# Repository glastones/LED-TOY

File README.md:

# LED-TOY
All led are blinking slow RGB. At the start all are uniform but after some time start to deviate. 
Nice to watch it.

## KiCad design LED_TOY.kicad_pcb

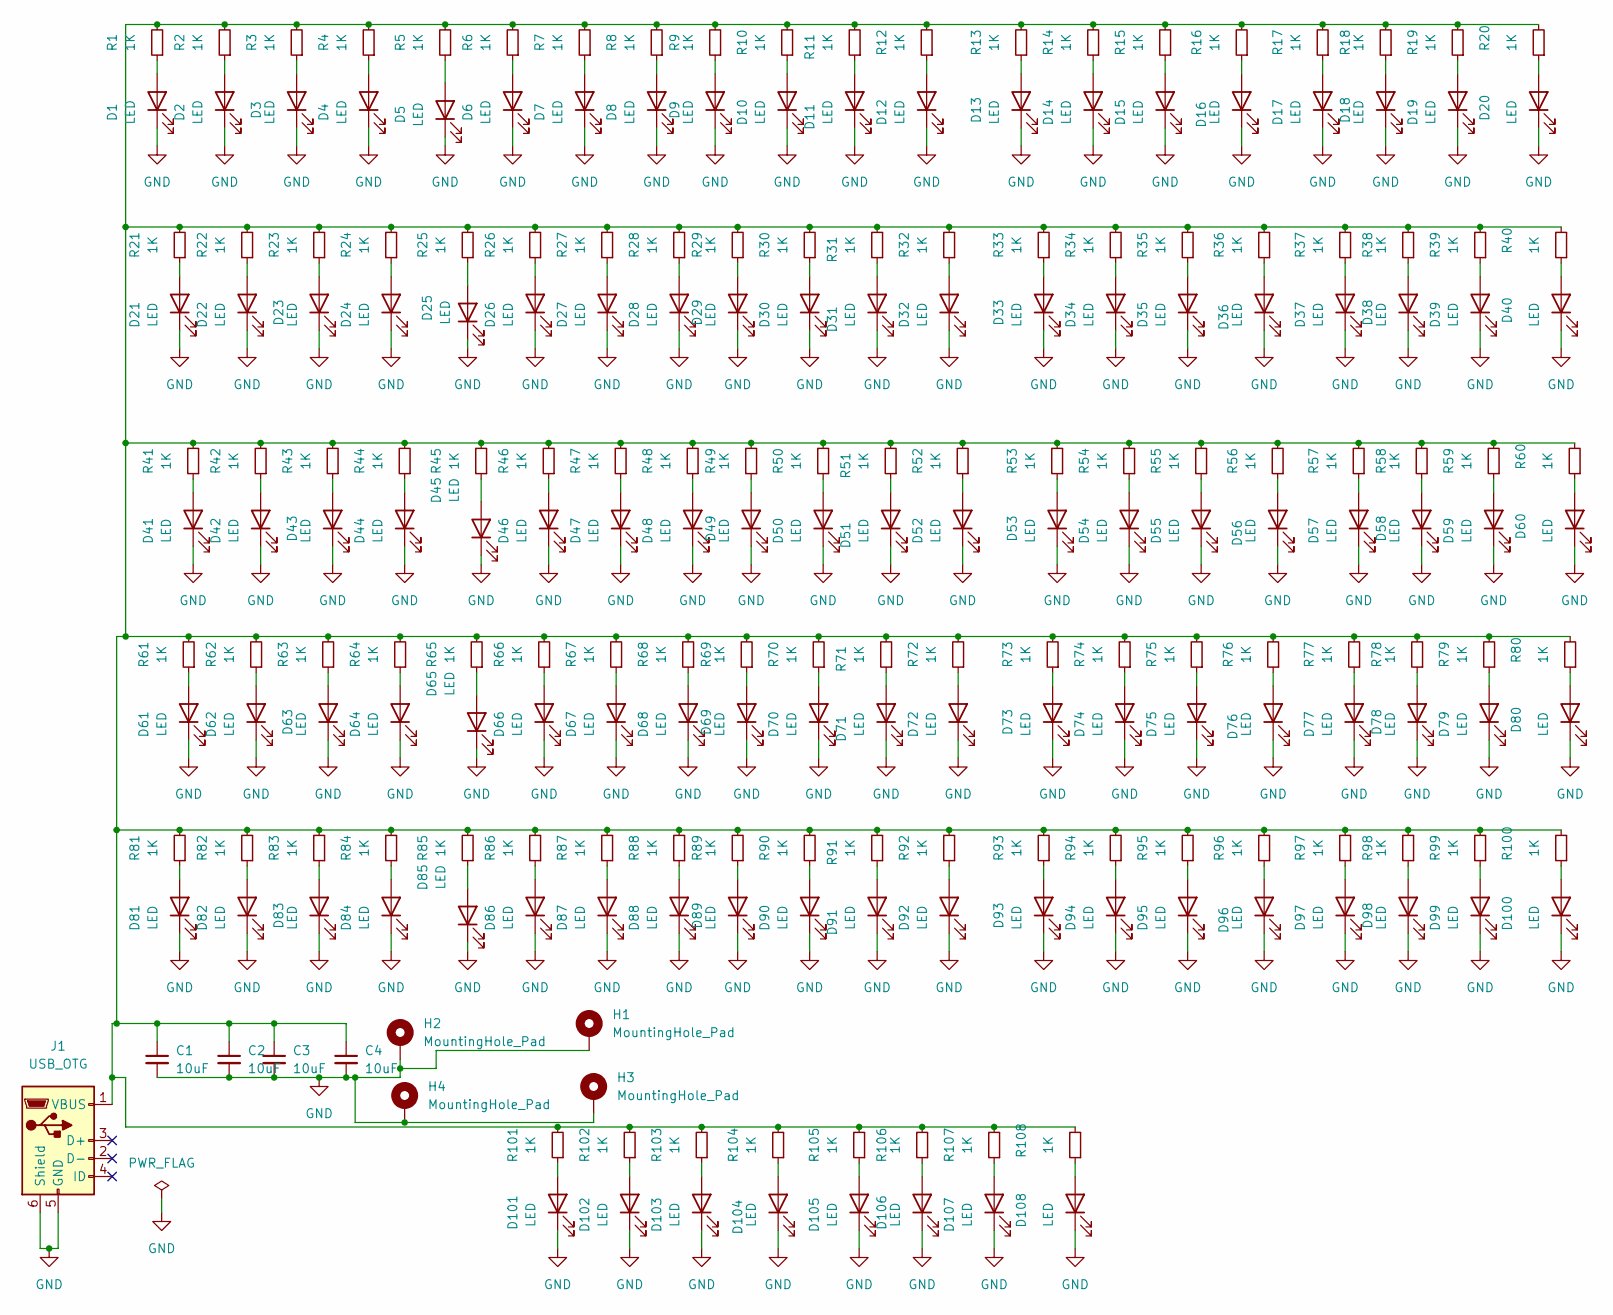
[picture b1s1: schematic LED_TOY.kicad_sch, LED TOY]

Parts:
C1, C2, C3, C4: 10uF; C_0805_2012Metric_Pad1.18x1.45mm_HandSolder
D1, D2, D3, D4, D5, D6, D7, D8, D9, D10, D11, D12, D13, D14, D15, D16, D17, D18, D19, D20, D21, D22, D23, D24, D25, D26, D27, D28, D29, D30, D31, D32, D33, D34, D35, D36, D37, D38, D39, D40, D41, D42, D43, D44, D45, D46, D47, D48, D49, D50, D51, D52, D53, D54, D55, D56, D57, D58, D59, D60, D61, D62, D63, D64, D65, D66, D67, D68, D69, D70, D71, D72, D73, D74, D75, D76, D77, D78, D79, D80, D81, D82, D83, D84, D85, D86, D87, D88, D89, D90, D91, D92, D93, D94, D95, D96, D97, D98, D99, D100, D101, D102, D103, D104, D105, D106, D107, D108: LED; LED_D5.0mm
H1, H2, H3, H4: MountingHole_Pad; MountingHole_2.7mm_Pad
J1: USB_OTG; USB_Mini-B_Lumberg_2486_01_Horizontal
R1, R2, R3, R4, R5, R6, R7, R8, R9, R10, R11, R12, R13, R14, R15, R16, R17, R18, R19, R20, R21, R22, R23, R24, R25, R26, R27, R28, R29, R30, R31, R32, R33, R34, R35, R36, R37, R38, R39, R40, R41, R42, R43, R44, R45, R46, R47, R48, R49, R50, R51, R52, R53, R54, R55, R56, R57, R58, R59, R60, R61, R62, R63, R64, R65, R66, R67, R68, R69, R70, R71, R72, R73, R74, R75, R76, R77, R78, R79, R80, R81, R82, R83, R84, R85, R86, R87, R88, R89, R90, R91, R92, R93, R94, R95, R96, R97, R98, R99, R100, R101, R102, R103, R104, R105, R106, R107, R108: 1K; R_0805_2012Metric_Pad1.20x1.40mm_HandSolder

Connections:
GND: C1.2, C2.2, C3.2, C4.2, D1.1 (K), D2.1 (K), D3.1 (K), D4.1 (K), D5.1 (K), D6.1 (K), D7.1 (K), D8.1 (K), D9.1 (K), D10.1 (K), D11.1 (K), D12.1 (K), D13.1 (K), D14.1 (K), D15.1 (K), D16.1 (K), D17.1 (K), D18.1 (K), D19.1 (K), D20.1 (K), D21.1 (K), D22.1 (K), D23.1 (K), D24.1 (K), D25.1 (K), D26.1 (K), D27.1 (K), D28.1 (K), D29.1 (K), D30.1 (K), D31.1 (K), D32.1 (K), D33.1 (K), D34.1 (K), D35.1 (K), D36.1 (K), D37.1 (K), D38.1 (K), D39.1 (K), D40.1 (K), D41.1 (K), D42.1 (K), D43.1 (K), D44.1 (K), D45.1 (K), D46.1 (K), D47.1 (K), D48.1 (K), D49.1 (K), D50.1 (K), D51.1 (K), D52.1 (K), D53.1 (K), D54.1 (K), D55.1 (K), D56.1 (K), D57.1 (K), D58.1 (K), D59.1 (K), D60.1 (K), D61.1 (K), D62.1 (K), D63.1 (K), D64.1 (K), D65.1 (K), D66.1 (K), D67.1 (K), D68.1 (K), D69.1 (K), D70.1 (K), D71.1 (K), D72.1 (K), D73.1 (K), D74.1 (K), D75.1 (K), D76.1 (K), D77.1 (K), D78.1 (K), D79.1 (K), D80.1 (K), D81.1 (K), D82.1 (K), D83.1 (K), D84.1 (K), D85.1 (K), D86.1 (K), D87.1 (K), D88.1 (K), D89.1 (K), D90.1 (K), D91.1 (K), D92.1 (K), D93.1 (K), D94.1 (K), D95.1 (K), D96.1 (K), D97.1 (K), D98.1 (K), D99.1 (K), D100.1 (K), D101.1 (K), D102.1 (K), D103.1 (K), D104.1 (K), D105.1 (K), D106.1 (K), D107.1 (K), D108.1 (K), H1.1, H2.1, H3.1, H4.1, J1.5 (GND), J1.6 (Shield)
unnamed: C1.1, C2.1, C3.1, C4.1, J1.1 (VBUS), R1.2, R2.2, R3.2, R4.2, R5.2, R6.2, R7.2, R8.2, R9.2, R10.2, R11.2, R12.2, R13.2, R14.2, R15.2, R16.2, R17.2, R18.2, R19.2, R20.2, R21.2, R22.2, R23.2, R24.2, R25.2, R26.2, R27.2, R28.2, R29.2, R30.2, R31.2, R32.2, R33.2, R34.2, R35.2, R36.2, R37.2, R38.2, R39.2, R40.2, R41.2, R42.2, R43.2, R44.2, R45.2, R46.2, R47.2, R48.2, R49.2, R50.2, R51.2, R52.2, R53.2, R54.2, R55.2, R56.2, R57.2, R58.2, R59.2, R60.2, R61.2, R62.2, R63.2, R64.2, R65.2, R66.2, R67.2, R68.2, R69.2, R70.2, R71.2, R72.2, R73.2, R74.2, R75.2, R76.2, R77.2, R78.2, R79.2, R80.2, R81.2, R82.2, R83.2, R84.2, R85.2, R86.2, R87.2, R88.2, R89.2, R90.2, R91.2, R92.2, R93.2, R94.2, R95.2, R96.2, R97.2, R98.2, R99.2, R100.2, R101.2, R102.2, R103.2, R104.2, R105.2, R106.2, R107.2, R108.2
unnamed: D1.2 (A), R1.1
unnamed: D2.2 (A), R2.1
unnamed: D3.2 (A), R3.1
unnamed: D4.2 (A), R4.1
unnamed: D5.2 (A), R5.1
unnamed: D6.2 (A), R6.1
unnamed: D7.2 (A), R7.1
unnamed: D8.2 (A), R8.1
unnamed: D9.2 (A), R9.1
unnamed: D10.2 (A), R10.1
unnamed: D11.2 (A), R11.1
unnamed: D12.2 (A), R12.1
unnamed: D13.2 (A), R13.1
unnamed: D14.2 (A), R14.1
unnamed: D15.2 (A), R15.1
unnamed: D16.2 (A), R16.1
unnamed: D17.2 (A), R17.1
unnamed: D18.2 (A), R18.1
unnamed: D19.2 (A), R19.1
unnamed: D20.2 (A), R20.1
unnamed: D21.2 (A), R21.1
unnamed: D22.2 (A), R22.1
unnamed: D23.2 (A), R23.1
unnamed: D24.2 (A), R24.1
unnamed: D25.2 (A), R25.1
unnamed: D26.2 (A), R26.1
unnamed: D27.2 (A), R27.1
unnamed: D28.2 (A), R28.1
unnamed: D29.2 (A), R29.1
unnamed: D30.2 (A), R30.1
unnamed: D31.2 (A), R31.1
unnamed: D32.2 (A), R32.1
unnamed: D33.2 (A), R33.1
unnamed: D34.2 (A), R34.1
unnamed: D35.2 (A), R35.1
unnamed: D36.2 (A), R36.1
unnamed: D37.2 (A), R37.1
unnamed: D38.2 (A), R38.1
unnamed: D39.2 (A), R39.1
unnamed: D40.2 (A), R40.1
unnamed: D41.2 (A), R41.1
unnamed: D42.2 (A), R42.1
unnamed: D43.2 (A), R43.1
unnamed: D44.2 (A), R44.1
unnamed: D45.2 (A), R45.1
unnamed: D46.2 (A), R46.1
unnamed: D47.2 (A), R47.1
unnamed: D48.2 (A), R48.1
unnamed: D49.2 (A), R49.1
unnamed: D50.2 (A), R50.1
unnamed: D51.2 (A), R51.1
unnamed: D52.2 (A), R52.1
unnamed: D53.2 (A), R53.1
unnamed: D54.2 (A), R54.1
unnamed: D55.2 (A), R55.1
unnamed: D56.2 (A), R56.1
unnamed: D57.2 (A), R57.1
unnamed: D58.2 (A), R58.1
unnamed: D59.2 (A), R59.1
unnamed: D60.2 (A), R60.1
unnamed: D61.2 (A), R61.1
unnamed: D62.2 (A), R62.1
unnamed: D63.2 (A), R63.1
unnamed: D64.2 (A), R64.1
unnamed: D65.2 (A), R65.1
unnamed: D66.2 (A), R66.1
unnamed: D67.2 (A), R67.1
unnamed: D68.2 (A), R68.1
unnamed: D69.2 (A), R69.1
unnamed: D70.2 (A), R70.1
unnamed: D71.2 (A), R71.1
unnamed: D72.2 (A), R72.1
unnamed: D73.2 (A), R73.1
unnamed: D74.2 (A), R74.1
unnamed: D75.2 (A), R75.1
unnamed: D76.2 (A), R76.1
unnamed: D77.2 (A), R77.1
unnamed: D78.2 (A), R78.1
unnamed: D79.2 (A), R79.1
unnamed: D80.2 (A), R80.1
unnamed: D81.2 (A), R81.1
unnamed: D82.2 (A), R82.1
unnamed: D83.2 (A), R83.1
unnamed: D84.2 (A), R84.1
unnamed: D85.2 (A), R85.1
unnamed: D86.2 (A), R86.1
unnamed: D87.2 (A), R87.1
unnamed: D88.2 (A), R88.1
unnamed: D89.2 (A), R89.1
unnamed: D90.2 (A), R90.1
unnamed: D91.2 (A), R91.1
unnamed: D92.2 (A), R92.1
unnamed: D93.2 (A), R93.1
unnamed: D94.2 (A), R94.1
unnamed: D95.2 (A), R95.1
unnamed: D96.2 (A), R96.1
unnamed: D97.2 (A), R97.1
unnamed: D98.2 (A), R98.1
unnamed: D99.2 (A), R99.1
unnamed: D100.2 (A), R100.1
unnamed: D101.2 (A), R101.1
unnamed: D102.2 (A), R102.1
unnamed: D103.2 (A), R103.1
unnamed: D104.2 (A), R104.1
unnamed: D105.2 (A), R105.1
unnamed: D106.2 (A), R106.1
unnamed: D107.2 (A), R107.1
unnamed: D108.2 (A), R108.1

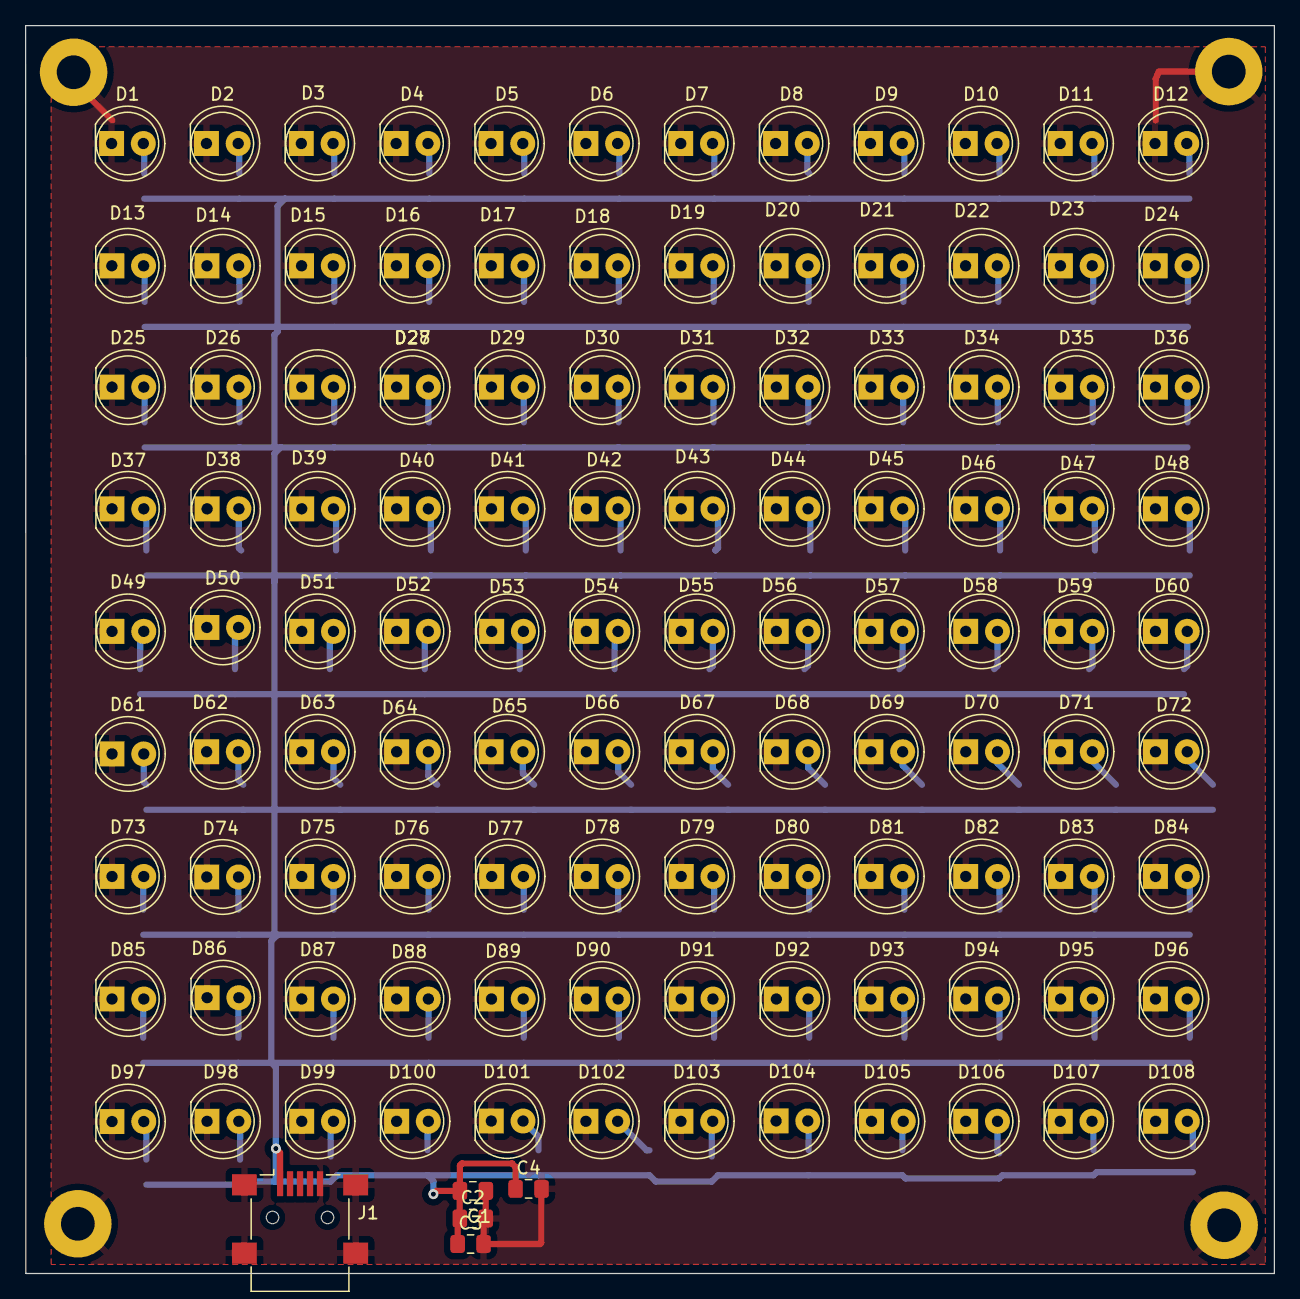
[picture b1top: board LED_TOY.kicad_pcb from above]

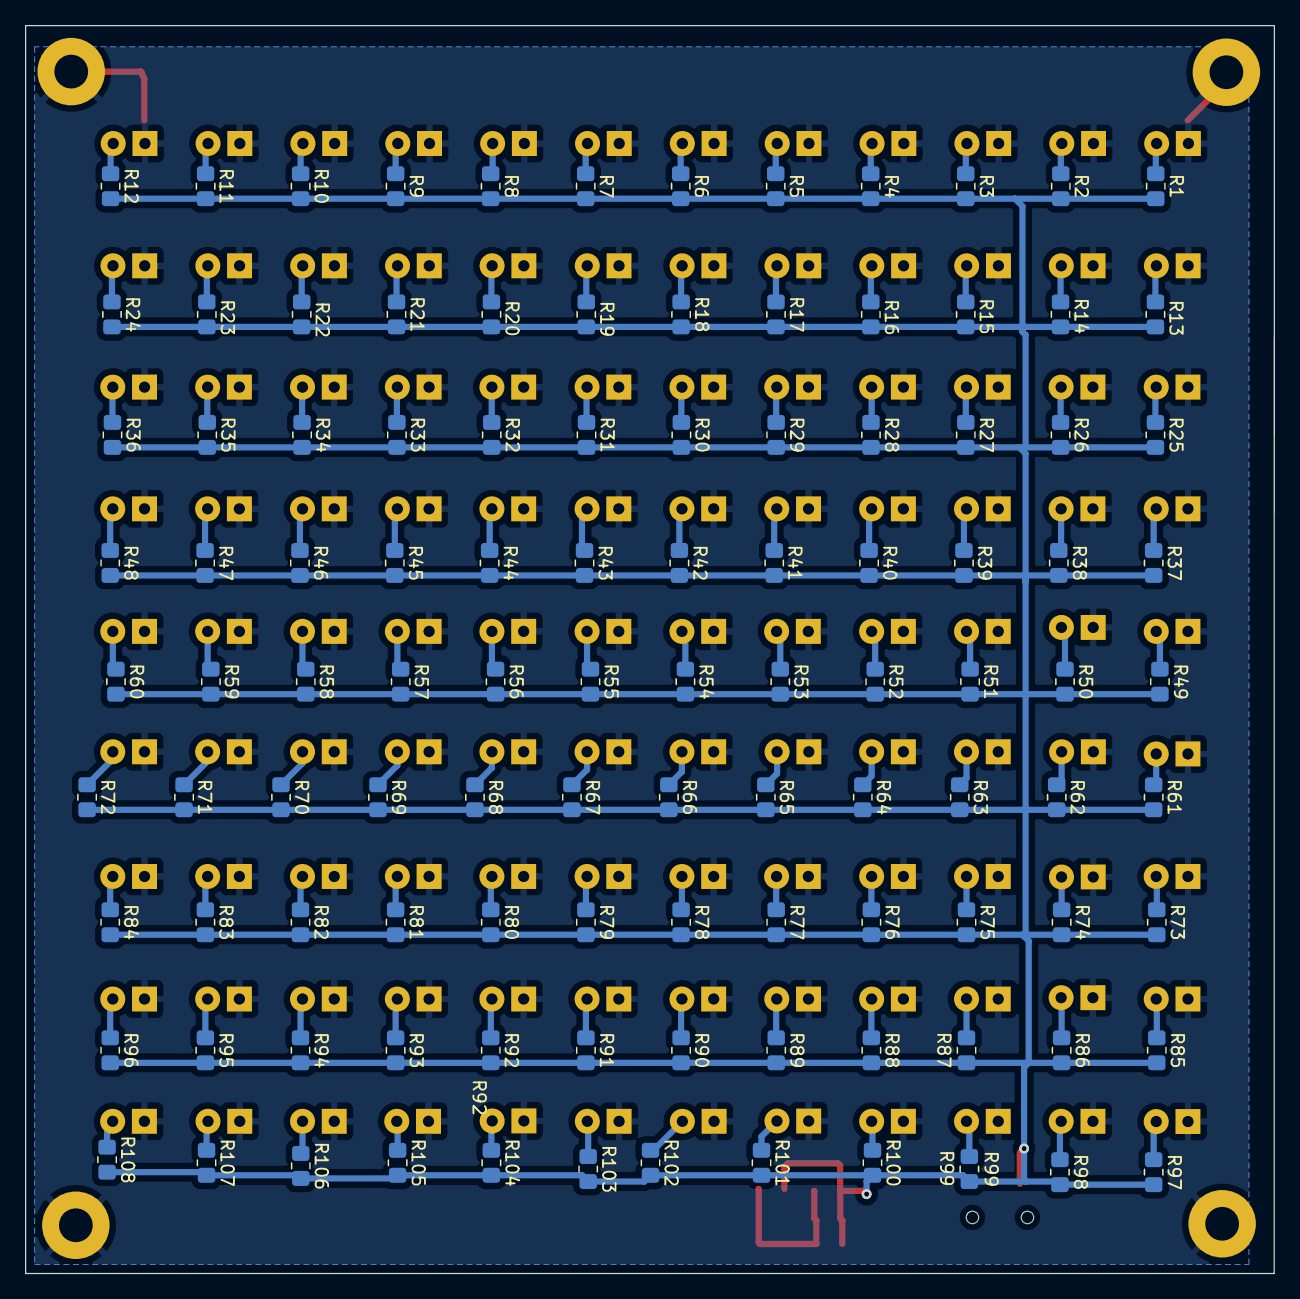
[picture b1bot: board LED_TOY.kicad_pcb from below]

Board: 2 copper layers, 99.9 x 99.9 mm, 225 parts (108 on the bottom side), 110 nets.

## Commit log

2024-12-10 Create LICENSE
2024-12-10 Update LICENSE
